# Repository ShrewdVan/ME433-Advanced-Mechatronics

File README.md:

# ME433-Advanced-Mechatronics
This repository is set for the Advanced Mechatronics course, ME 433 in Northwestern Univerisity in 2025.

The Assignment 1 is focusing on the basic use of github.

The Assignment 2 is a entry level led project with periphrial interrupt service.

The Assignment 3 is a project combining usb CDC, GPIO, and ADC to perform a voltage sensor CUL.

The Assignment 4 is a project talking to the dac to generate a 2 Hz sin wave and a 1 Hz triangle wave simultaneously with spi as the communication protocol.

The Assignment 5 is a project using SPI as the protocol to communicate 2 devices, a Dac and a RAM. fill 1000 sample points into RAM first, then read from RAM and write to dac to create a sin wave.

The Assignment 6 is a project using I2C to communicate with a I/O Expander, read from one specific input pin and control the logic level of another output pin using SPI to overwrite its logic value in register.

The Assignment 7 is a project using I2C to control a oled screen to display the voltage information measured by an analog-to-digital converter.

The Assignment 8 is a project using PIO to send specific signal to control the ws2812 addressable led series, and PWM periphrial to control a servo motor.

The Assignment 9 is a tiny project related to the dual core cooperation to finish three small tasks: read the adc, turn on and turn off the specific led.

The Assignment 10 is to get fimiliar with the signal processing, low-pass filter for here. Use MAF, IIR and FIR to filter the data with a balence between smooth and noise elimination.

The Assignment 11 is to emulate the pico board to be a mouse. By sending the hid-mouse report to the pc, we can control the cursor by hitting the button, control its speed or acceleration, even change the mode of the cursor's movement.

The Assignment 12 is to get to know how a camera work, including row synch and frame synch with bunch of interrupt and flag control. Take the data from camera, send to pico, then send to PC and finally processed by python to see the image.

The Assignment 13 is to play with the Imu unit. There are 2 parts of the assignment, (1) Display the board movement by drawing the line to the direction it tilts (2) Combine the Imu unit with the Mouse, make a special mouse which can be controlled by tilting the board with 2 buttons acting as the left and right click button.

The content will be implemented as the course processes.

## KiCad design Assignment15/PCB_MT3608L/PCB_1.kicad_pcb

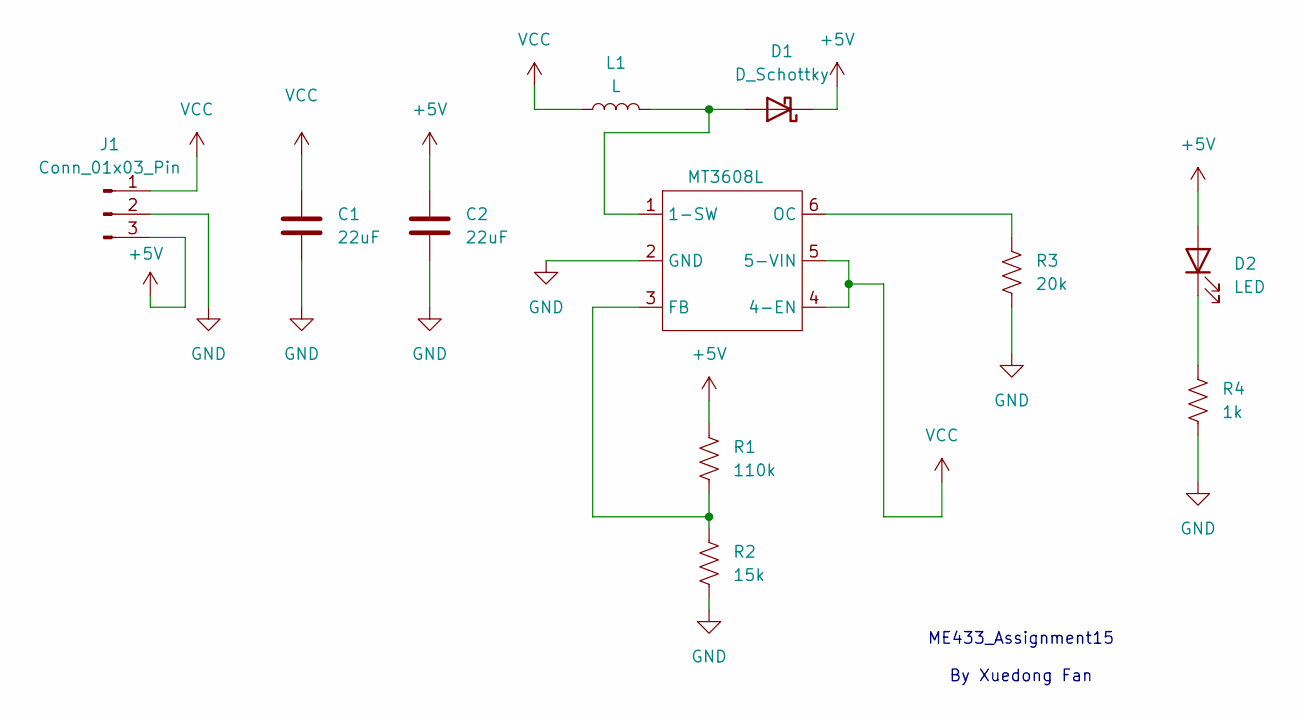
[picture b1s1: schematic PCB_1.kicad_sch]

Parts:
C1, C2: 22uF; C_0805_2012Metric
D1: D_Schottky; D_SOD-123
D2: LED; LED_0603_1608Metric
J1: Conn_01x03_Pin; PinSocket_1x03_P2.54mm_Vertical
L1: L; L_1210_3225Metric
MT3608L: SOT-23-6
R1: 110k; R_0805_2012Metric
R2: 15k; R_0805_2012Metric
R3: 20k; R_0805_2012Metric
R4: 1k; R_0805_2012Metric

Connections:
+5V: C2.1, D1.1 (K), D2.2 (A), J1.3, R1.1
GND: C1.2, C2.2, J1.2, MT3608L.2 (GND), R2.2, R3.2, R4.2
unnamed: D1.2 (A), L1.2, MT3608L.1 (1-SW)
unnamed: D2.1 (K), R4.1
unnamed: MT3608L.3 (FB), R1.2, R2.1
unnamed: MT3608L.6 (OC), R3.1
VCC: C1.1, J1.1, L1.1, MT3608L.4 (4-EN), MT3608L.5 (5-VIN)

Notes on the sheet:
ME433_Assignment15 By Xuedong Fan

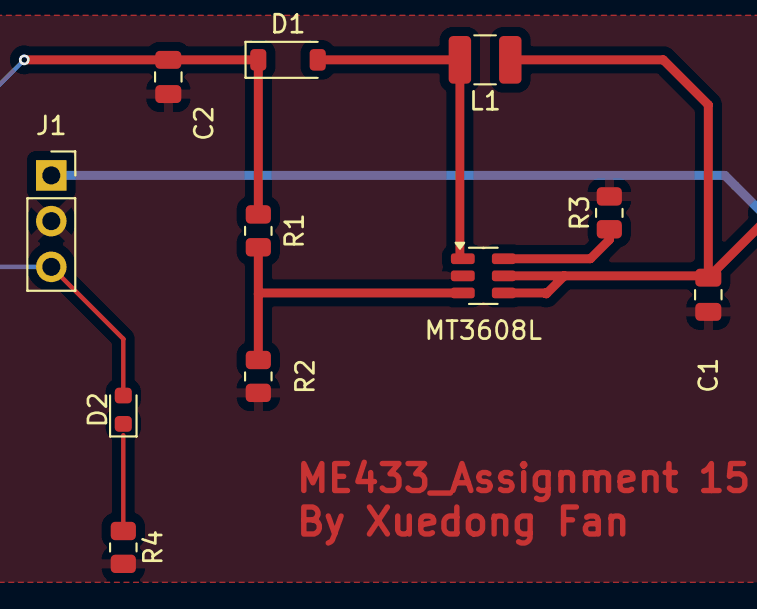
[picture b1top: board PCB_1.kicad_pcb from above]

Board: 2 copper layers, 11 parts (0 on the bottom side), 7 nets.

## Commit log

2025-04-06 to cloud
2025-04-08 timepoint (HW2 completed)
2025-04-08 timepoint_1 (HW2 completed)
2025-04-08 timepoint_2 (HW2_completed)
2025-04-08 timepoint (HW2 completed wiz demo)
2025-04-10 timepoint (HW3 completed)
2025-04-10 timepoint_1 (HW3 completed with demo)
2025-04-15 timepoint(HW4 complete)
2025-04-15 timepoint_1 (Hw 4 completes)
2025-04-15 timepoint_2(Hw4 complets with demo)
2025-04-17 timepoint_0 (HW5 part1 complete)
2025-04-18 timepoint2 (HW5 completes)
2025-04-22 timepoint(HW6 completes with demo)
2025-04-24 timepoint0(HW7 completes with demo)
2025-04-29 timepoint(HW 8 completes with demo)
2025-04-30 timepoint(HW9 completes with demo)
2025-05-04 timepoint(HW10 completes)
2025-05-09 timepoint(HW11 completes with demo)
2025-05-14 timepoint(camera code )
2025-05-16 timepoint(Completes with the demo)
2025-05-20 timepoint(HW13 with bouns)
2025-05-23 Timepoint(Assignment 16)
